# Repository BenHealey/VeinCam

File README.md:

# VeinCam

VeinCam is an educational tool for vein visualisation. It uses near infrared (nIR) light and a nIR-sensitive camera to stream a real-time vein-enhanced video image to a user's phone or tablet. In addition to a custom PCB to control the nIR light source, the device employs widely available low-cost components from the [Raspberry Pi educational foundation](https://www.raspberrypi.org/).

VeinCam is *not* a certified medical device and is therefore not intended for use in a clinical setting.

---
## Contents
1. [Development History](###1-development-history)
2. [Structure of the Repository](###2-structure-of-the-repository)
3. [Hardware Kit](###3-hardware-kit)

---
### 1. Development History
Much of VeinCam's development occurred during [ANU Engineering](https://cs.anu.edu.au/TechLauncher/) capstone projects in 2018 and 2019. Created as an open-source project, anyone who may find VeinCam useful for learning can get the information necessary to make one for their own personal use in this GitHub repository.

### 2. Structure of the Repository
The repository is broadly split into Hardware and Software sections.

Each section contains schematics or code for the components of the device. The root folders for each section contain *readme* files outlining their contents and key aspects of functionality. The *assembly* instructions in each folder outline at a high level how to get the device working.

Please note that while the software licence is GPL3.0, the hardware specifications are intended to be available for personal non-commercial use one. Only the developers may create commercial versions of the VeinCam hardware for sale to others.

### 3. Hardware Kit
Many people will not have access to the equipment required to make the hardware components of the device, so we are in the process of finalising a low-cost kit you can purchase. (due end of 2019)

You can check availability at the [VeinCam Hardware Kit website](https://veincam.com/).

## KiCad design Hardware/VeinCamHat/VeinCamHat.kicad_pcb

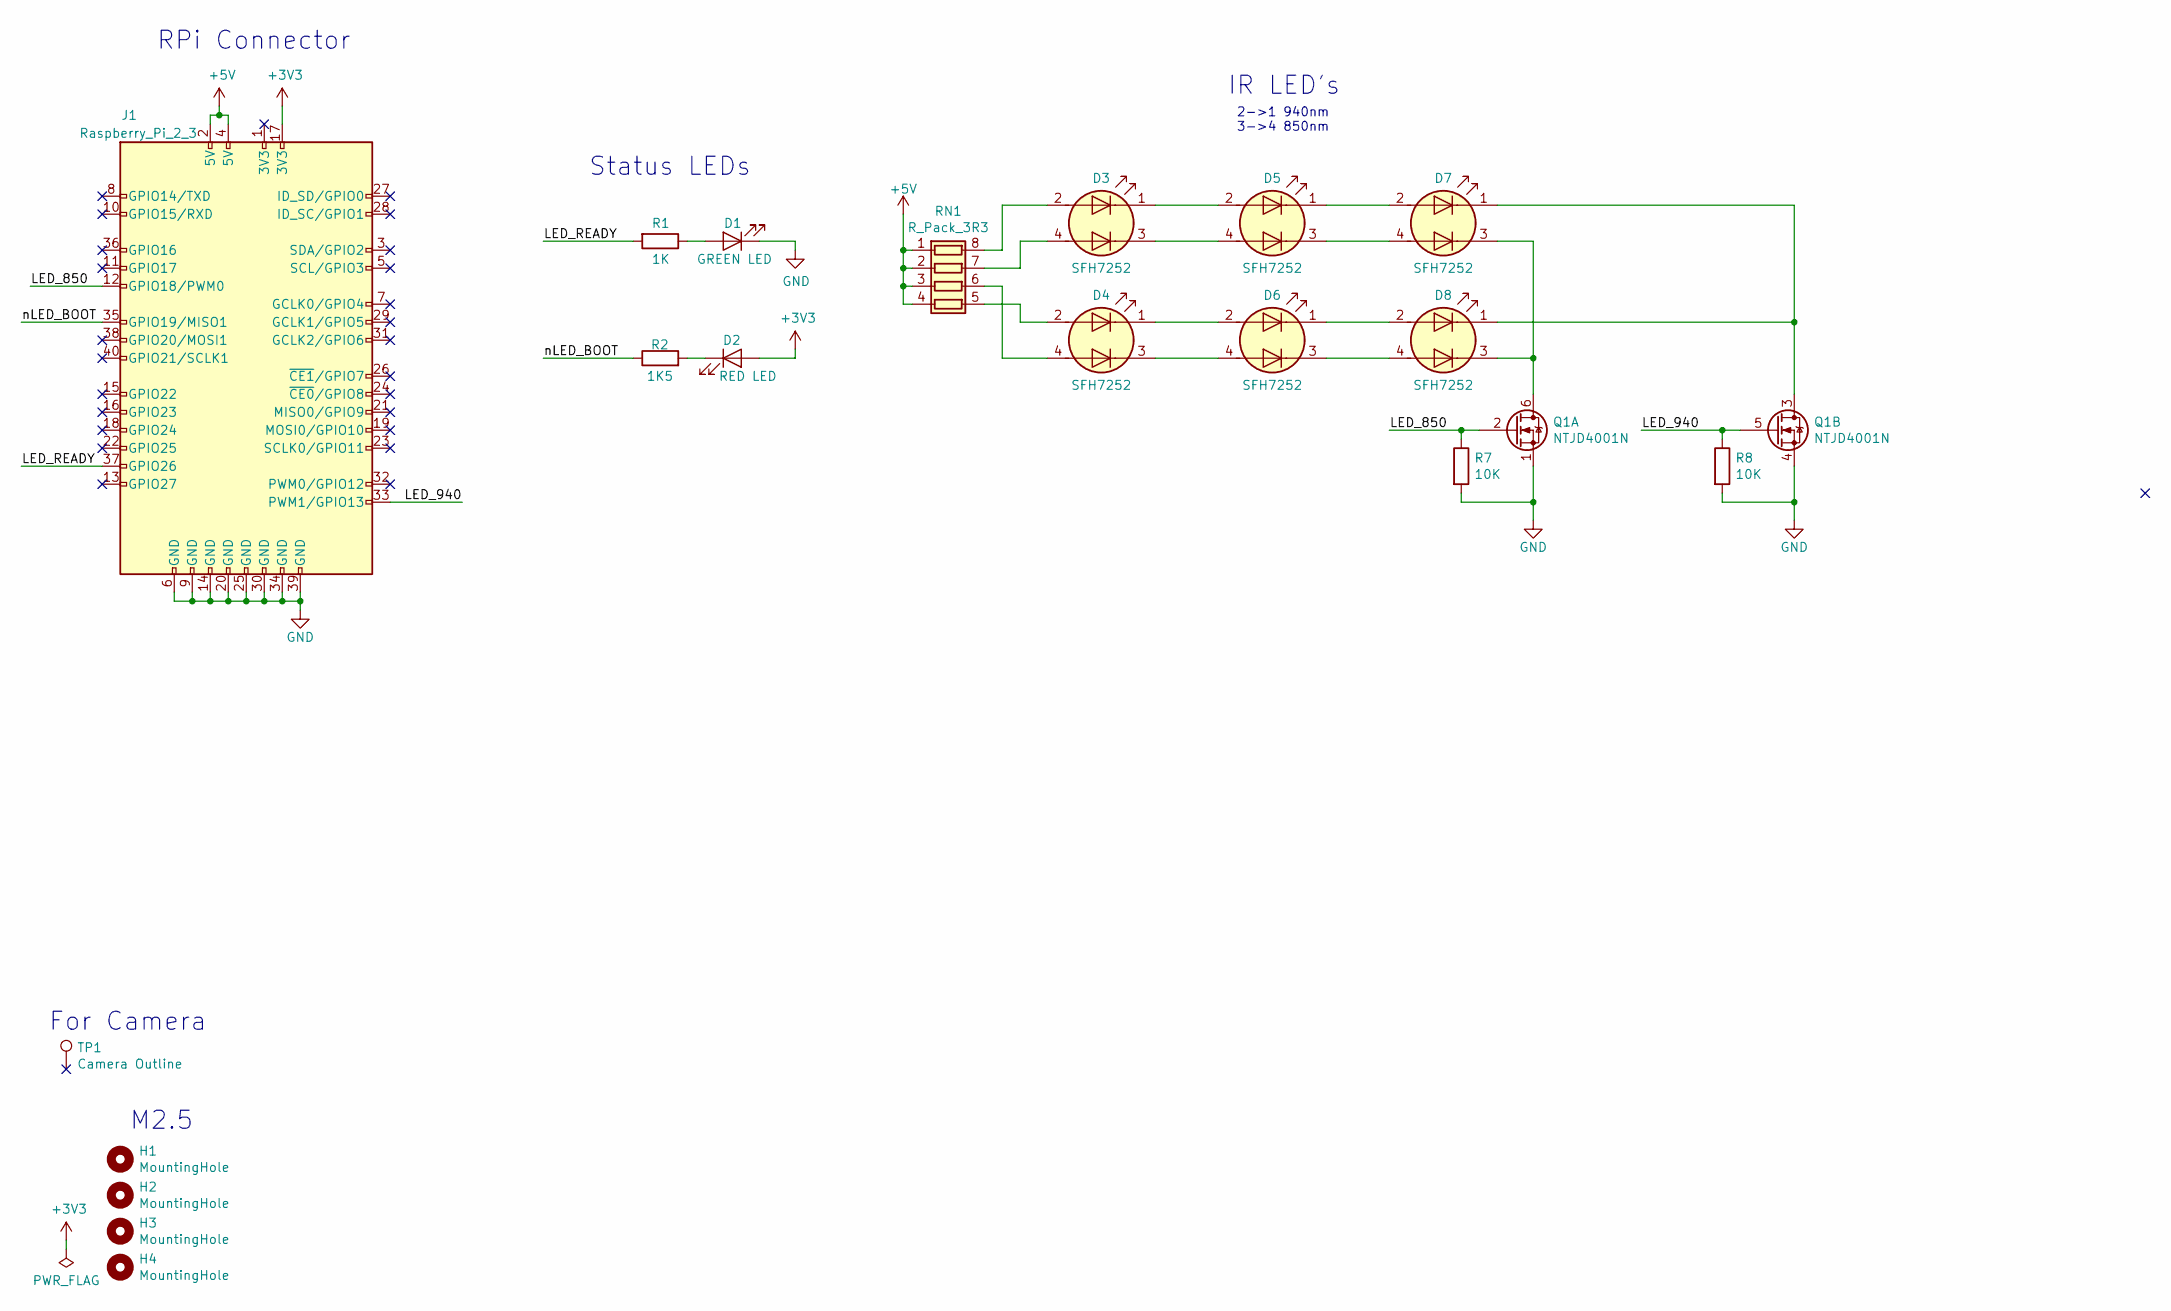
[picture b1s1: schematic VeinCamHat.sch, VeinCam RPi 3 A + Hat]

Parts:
D1: GREEN LED; LED_0805_2012Metric
D2: RED LED; LED_0805_2012Metric
D3, D4, D5, D6, D7, D8: SFH7252
H1, H2, H3, H4: MountingHole; MountingHole_2.7mm_M2.5
J1: Raspberry_Pi_2_3; PinSocket_2x20_P2.54mm_Vertical
Q1: NTJD4001N; SOT-363_SC-70-6
R1: 1K; R_0603_1608Metric
R2: 1K5; R_0603_1608Metric
R7, R8: 10K; R_0603_1608Metric
RN1: R_Pack_3R3; R_Array_Convex_4x0603
TP1: Camera Outline; PiCamera

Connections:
+3V3: D2.2 (A), J1.17 (3V3)
+5V: J1.2 (5V), J1.4 (5V), RN1.1 (R1.1), RN1.2 (R2.1), RN1.3 (R3.1), RN1.4 (R4.1)
/LED_850: J1.12 (GPIO18/PWM0), Q1.2 (G), R7.1
/LED_940: J1.33 (PWM1/GPIO13), Q1.5 (G), R8.1
/LED_READY: J1.37 (GPIO26), R1.2
/nLED_BOOT: J1.35 (GPIO19/MISO1), R2.1
GND: D1.1 (K), J1.6 (GND), J1.9 (GND), J1.14 (GND), J1.20 (GND), J1.25 (GND), J1.30 (GND), J1.34 (GND), J1.39 (GND), Q1.1 (S), Q1.4 (S), R7.2, R8.2
unnamed: D1.2 (A), R1.1
unnamed: D2.1 (K), R2.2
unnamed: D3.1 (K2), D5.2 (A2)
unnamed: D3.2 (A2), RN1.8 (R1.2)
unnamed: D3.3 (K1), D5.4 (A1)
unnamed: D3.4 (A1), RN1.7 (R2.2)
unnamed: D4.1 (K2), D6.2 (A2)
unnamed: D4.2 (A2), RN1.5 (R4.2)
unnamed: D4.3 (K1), D6.4 (A1)
unnamed: D4.4 (A1), RN1.6 (R3.2)
unnamed: D5.1 (K2), D7.2 (A2)
unnamed: D5.3 (K1), D7.4 (A1)
unnamed: D6.1 (K2), D8.2 (A2)
unnamed: D6.3 (K1), D8.4 (A1)
unnamed: D7.1 (K2), D8.1 (K2), Q1.3 (D)
unnamed: D7.3 (K1), D8.3 (K1), Q1.6 (D)

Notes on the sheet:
RPi Connector
M2.5
IR LED's
2->1 940nm 3->4 850nm
Status LEDs
For Camera

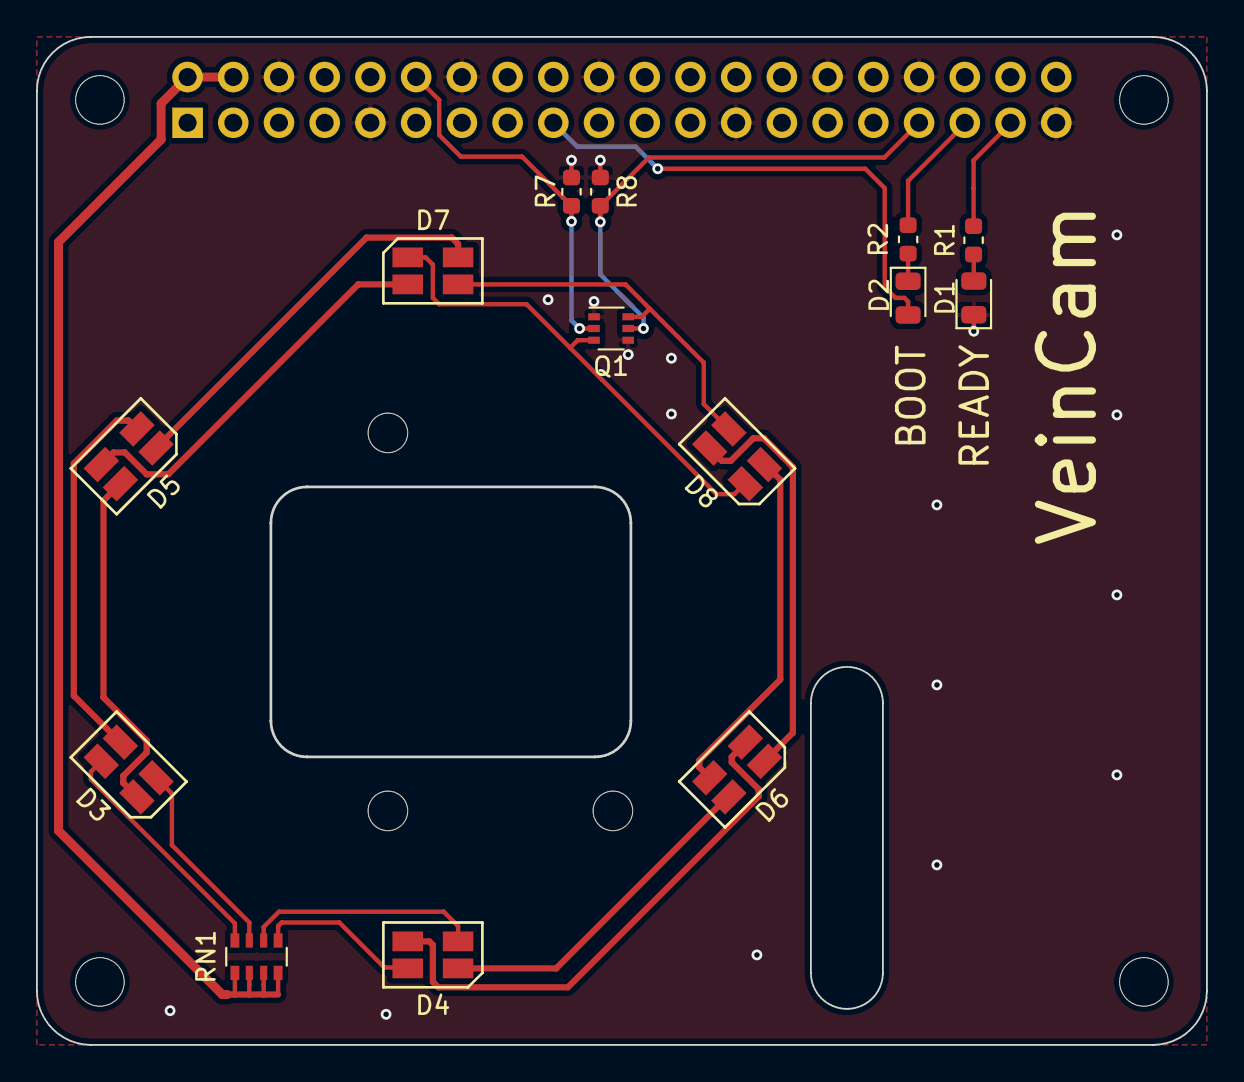
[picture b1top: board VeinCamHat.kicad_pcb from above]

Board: 2 copper layers, 65.0 x 56.0 mm, 20 parts (1 on the bottom side), 23 nets.

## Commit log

2018-12-18 Initial transfer from ENG4221 project repo
2018-12-30 Set theme jekyll-theme-slate
2018-12-30 Update CNAME
2019-06-04 Clearing repo in advance of 2019 update
2019-06-04 Create CNAME
2019-06-04 Initial update from 2019 project
2019-06-04 General updates to project software after poster cutoff.
2019-06-04 Index update
2019-06-04 Index updates
2019-06-04 More index changes
2019-06-04 Index.
2019-06-05 Index update - simplification and style fixes.
2019-06-05 Completed version of .org landing.
2019-06-05 Adding assembly instructions. Minor typo edits elsewhere.
2019-06-07 Modifications to emulated and prod piopencv code - add HE function
2019-06-12 Image path updates
2019-06-12 Temporary buttons to test CLAHE filtering settings.
2019-06-15 Changes to default CLAHE settings - hard coded.
2019-06-15 Added wifi config change functionality.
2019-06-15 Changes to gitignore
2019-06-16 Fixed wifi setting warning, modifications to front end.
2019-06-16 Wifi pwd must have 8+characters
2019-06-17 Update to readme.
2019-06-17 Minor mod to readme.
2019-06-17 License info.
2019-06-17 Gitignore changes
